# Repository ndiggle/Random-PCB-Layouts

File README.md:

# Random-PCB-Layouts

## Objective
I've uploaded some PCB layouts that I've done in Eagle and KiCad over the past few months. The majority of these layouts were done for pedagogical purposes, but feel free to use any of the designs for alternate uses.

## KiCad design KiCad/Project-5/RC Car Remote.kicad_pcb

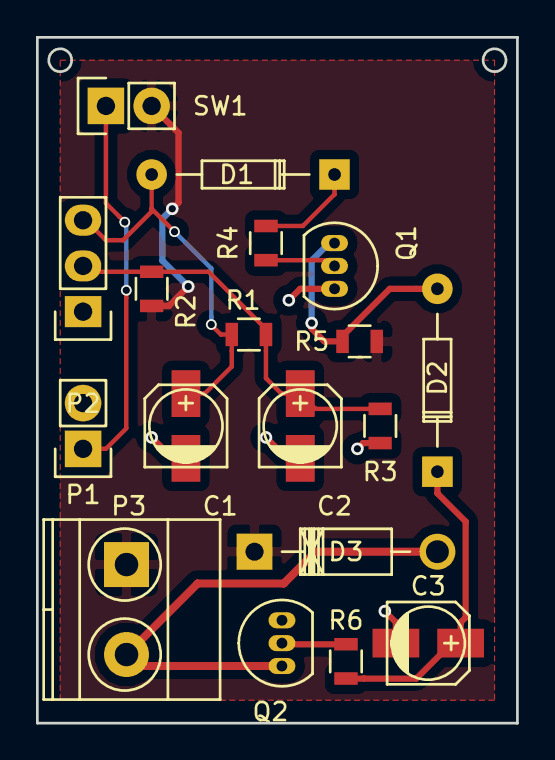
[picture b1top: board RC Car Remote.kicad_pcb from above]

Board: 2 copper layers, 26.7 x 38.1 mm, 18 parts (0 on the bottom side), 11 nets.

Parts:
C1: 47uF; c_elec_4x5.7
C2: 22uF; c_elec_4x5.7
C3: 4.7uF; c_elec_4x5.7
D1, D2: 1N4148; Diode_DO-35_SOD27_Horizontal_RM10
D3: 1N4007; Diode_DO-41_SOD81_Horizontal_RM10
P1: BATT; Pin_Header_Straight_1x02
P2: IR_Reciever; Pin_Header_Straight_1x03
P3: NC_Motor_Relay; TerminalBlock_Pheonix_MKDS1.5-2pol
Q1, Q2: BC548; TO-92_Inline_Narrow_Oval
R1: 33k; R_0805
R2: 560; R_0805
R3: 100k; R_0805
R4: 47k; R_0805
R5, R6: 10k; R_0805
SW1: SPST; Socket_Strip_Straight_1x02

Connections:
+6V: D3.1, P3.1, R2.1, R5.2, SW1.2
/Rly1: D3.2, P3.2, Q2.1
GND: C1.2, C2.2, C3.2, P1.2, P2.1, Q1.3, Q2.3, R3.2
IR_R_2: C2.1, P2.2, R1.1, R2.2, R3.1
IR_R_3: C1.1, D1.2, P2.3, R1.2
unnamed: C3.1, D2.1, R6.2
unnamed: D1.1, R4.2
unnamed: D2.2, Q1.1, R5.1
unnamed: P1.1, SW1.1
unnamed: Q1.2, R4.1
unnamed: Q2.2, R6.1

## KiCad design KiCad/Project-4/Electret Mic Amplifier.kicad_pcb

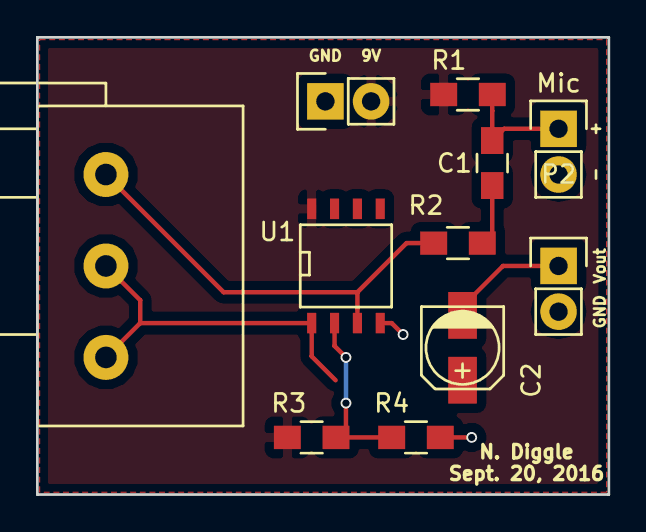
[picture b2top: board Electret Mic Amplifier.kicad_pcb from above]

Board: 2 copper layers, 31.8 x 25.4 mm, 11 parts (0 on the bottom side), 8 nets.

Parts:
C1: 0.1uF; C_0805_HandSoldering
C2: 4.7uF; c_elec_4x5.3
Mic: EM-6022P; Pin_Header_Straight_1x02
P1, P2: CONN_01X02; Pin_Header_Straight_1x02
R1, R3, R4: 10k; R_0805_HandSoldering
R2: 1k; R_0805_HandSoldering
RV1: 100k; Potentiometer_Alps-RK163-single_15mm
U1: LM358; SOIC-8-N

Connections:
+9V: P1.2, R1.1, R3.2, U1.8
/V+: R2.1, RV1.1, U1.3
/V-: R3.1, R4.2, U1.2
/Vfb: C2.1, RV1.2, RV1.3, U1.1
/Vin: C1.2, Mic.1, R1.2
/Vout: C2.2, P2.1
GND: Mic.2, P1.1, P2.2, R4.1, U1.4
unnamed: C1.1, R2.2

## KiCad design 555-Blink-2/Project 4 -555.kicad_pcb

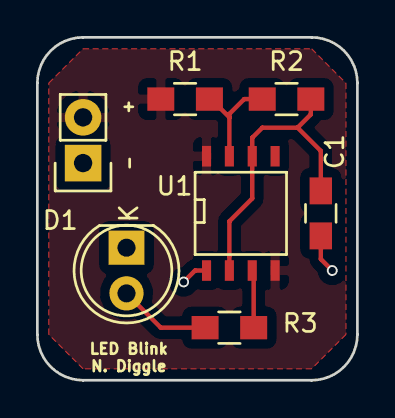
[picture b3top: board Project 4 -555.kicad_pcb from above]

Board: 2 copper layers, 17.8 x 19.0 mm, 7 parts (0 on the bottom side), 6 nets.

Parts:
C1: 1uF; C_0805_HandSoldering
D1: LED; LED-5MM
P1: CONN_01X02; Socket_Strip_Straight_1x02
R1, R3: 1k; R_0805_HandSoldering
R2: 470k; R_0805_HandSoldering
U1: ICM7555; SOIC-8-N

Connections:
GND: C1.2, D1.1, P1.1, U1.1
unnamed: C1.1, R2.2, U1.2, U1.6
unnamed: D1.2, R3.2
unnamed: R1.2, R2.1, U1.7
unnamed: R3.1, U1.3
VCC: P1.2, R1.1, U1.4, U1.8

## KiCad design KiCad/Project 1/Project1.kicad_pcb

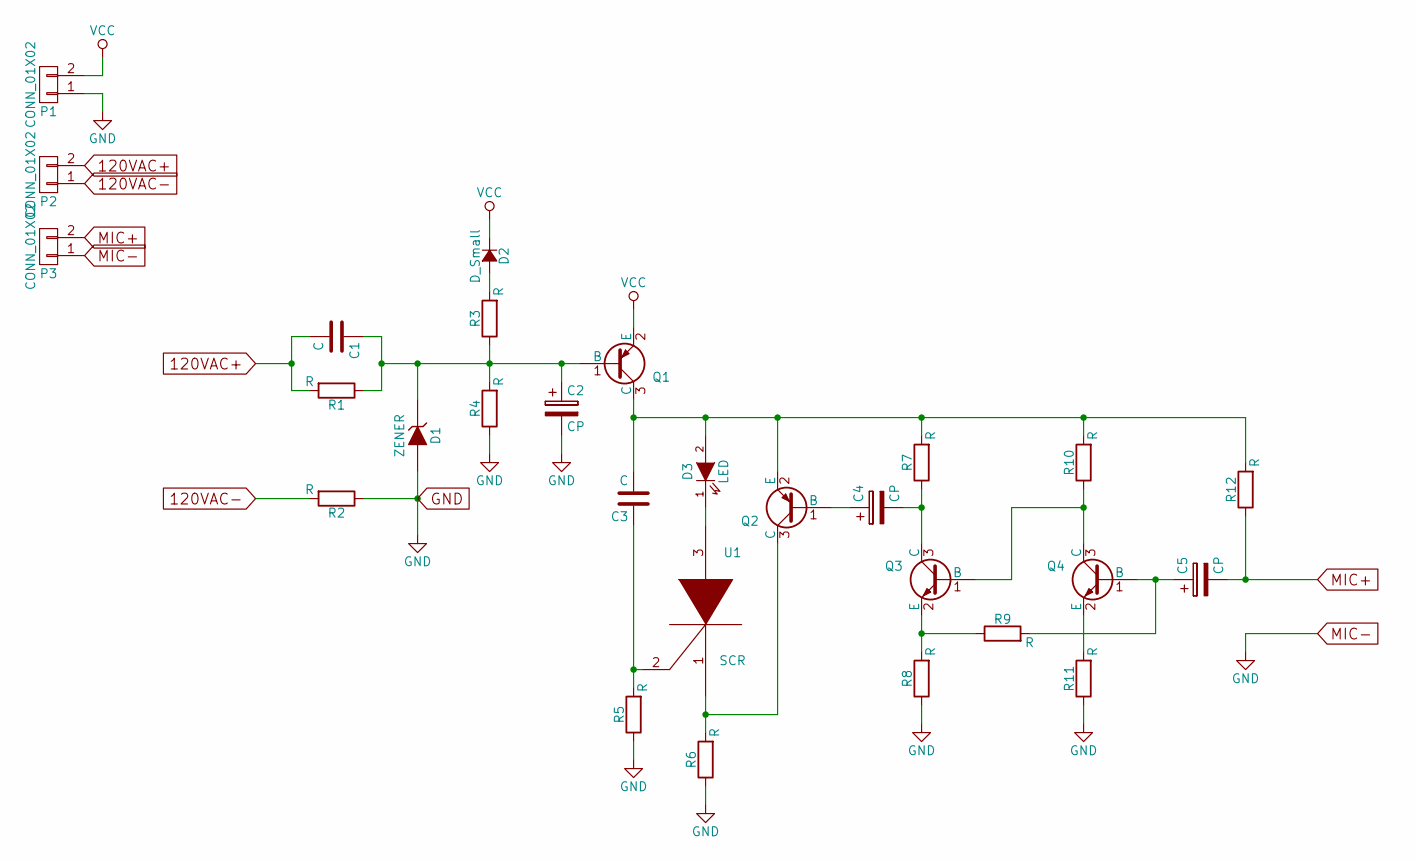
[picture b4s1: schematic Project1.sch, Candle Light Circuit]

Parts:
C1: C; c_elec_8x10
C2, C4, C5: CP; c_elec_8x10
C3: C; C_0805
D1: ZENER; SMB_Handsoldering
D2: D_Small; Diode_DO-41_SOD81_Vertical_AnodeUp
D3: LED; LED-5MM
P1, P2, P3: CONN_01X02; Pin_Header_Straight_1x02
Q1, Q2: MMBT3906; SOT-23_Handsoldering
Q3, Q4: MMBT3904; SOT-23_Handsoldering
R1, R2, R3, R4, R5, R6, R7, R8, R9, R10, R11, R12: R; R_0805_HandSoldering
U1: SCR; TO-220_Neutral123_Vertical

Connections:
120VAC+: C1.2, P2.2, R1.2
120VAC-: P2.1, R2.2
GND: C2.2, D1.2 (A), P1.1, P3.1, R2.1, R4.1, R5.1, R6.1, R8.1, R11.1
MIC+: C5.2, P3.2, R12.1
unnamed: C1.1, C2.1, D1.1 (K), Q1.1 (B), R1.1, R3.1, R4.2
unnamed: C3.1, R5.2, U1.2 (G)
unnamed: C3.2, D3.2 (A), Q1.3 (C), Q2.2 (E), R7.2, R10.2, R12.2
unnamed: C4.1, Q2.1 (B)
unnamed: C4.2, Q3.3 (C), R7.1
unnamed: C5.1, Q4.1 (B), R9.2
unnamed: D2.2 (A), R3.2
unnamed: D3.1 (K), U1.3 (A)
unnamed: Q2.3 (C), R6.2, U1.1 (K)
unnamed: Q3.1 (B), Q4.3 (C), R10.1
unnamed: Q3.2 (E), R8.2, R9.1
unnamed: Q4.2 (E), R11.2
VCC: D2.1 (K), P1.2, Q1.2 (E)

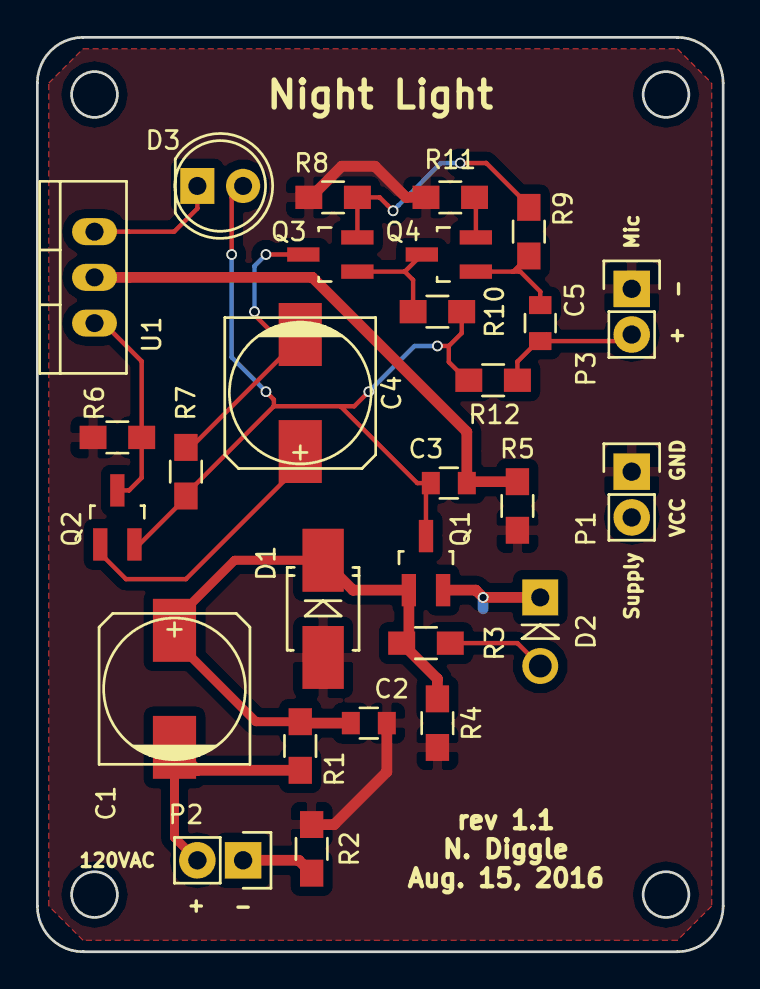
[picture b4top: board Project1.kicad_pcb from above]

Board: 2 copper layers, 38.1 x 50.8 mm, 28 parts (0 on the bottom side), 17 nets.

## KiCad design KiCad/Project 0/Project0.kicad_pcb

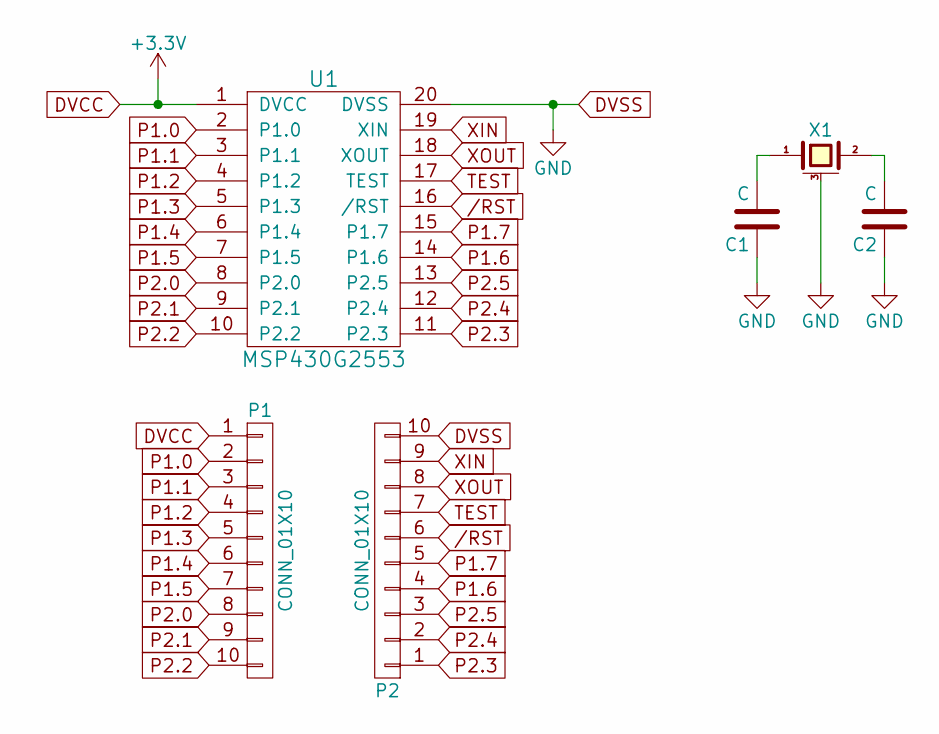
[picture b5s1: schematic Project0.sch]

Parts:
C1, C2: C; C_0805_HandSoldering
P1, P2: CONN_01X10; Pin_Header_Straight_1x10
U1: MSP430G2553; SSOP-20
X1: CRYSTAL_SMD; Crystal_HC49-U_Vertical_3Pin

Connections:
/RST: P2.6, U1.16 (/RST)
DVCC: P1.1, U1.1 (DVCC)
DVSS: C1.1, C2.1, P2.10, U1.20 (DVSS), X1.3 (case)
unnamed: C1.2, X1.1
unnamed: C2.2, X1.2
P1.0: P1.2, U1.2 (P1.0)
P1.1: P1.3, U1.3 (P1.1)
P1.2: P1.4, U1.4 (P1.2)
P1.3: P1.5, U1.5 (P1.3)
P1.4: P1.6, U1.6 (P1.4)
P1.5: P1.7, U1.7 (P1.5)
P1.6: P2.4, U1.14 (P1.6)
P1.7: P2.5, U1.15 (P1.7)
P2.0: P1.8, U1.8 (P2.0)
P2.1: P1.9, U1.9 (P2.1)
P2.2: P1.10, U1.10 (P2.2)
P2.3: P2.1, U1.11 (P2.3)
P2.4: P2.2, U1.12 (P2.4)
P2.5: P2.3, U1.13 (P2.5)
TEST: P2.7, U1.17 (TEST)
XIN: P2.9, U1.19 (XIN)
XOUT: P2.8, U1.18 (XOUT)

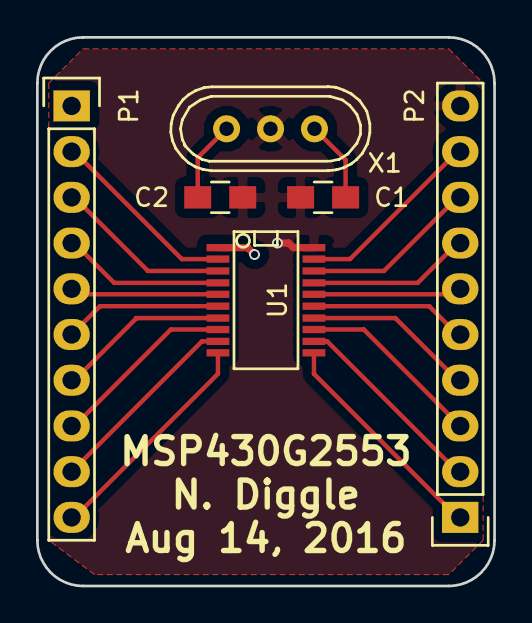
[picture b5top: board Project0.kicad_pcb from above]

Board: 2 copper layers, 25.4 x 30.5 mm, 6 parts (0 on the bottom side), 22 nets.

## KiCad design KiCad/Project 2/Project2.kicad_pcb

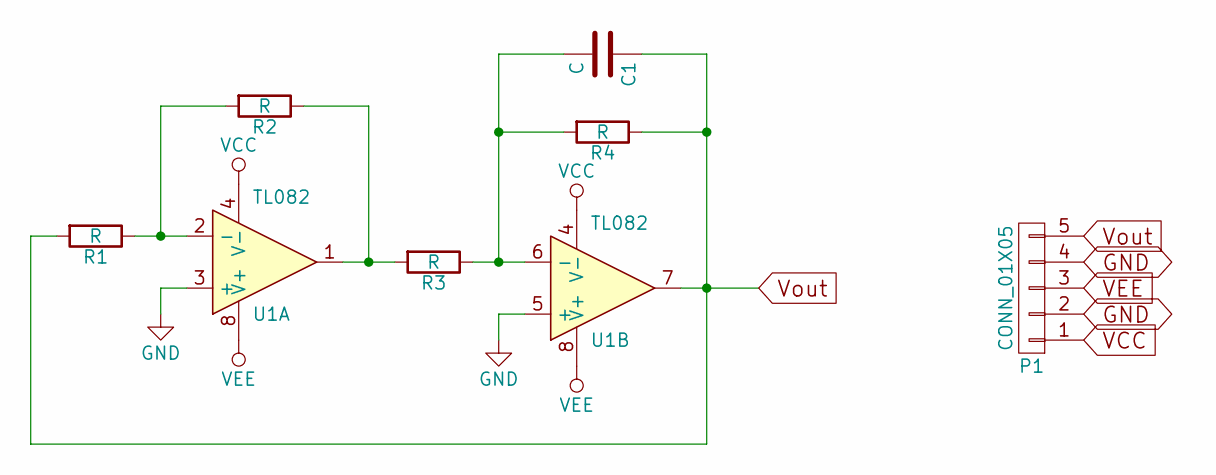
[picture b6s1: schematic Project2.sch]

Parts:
C1: C; C_0805_HandSoldering
P1: CONN_01X05; Pin_Header_Straight_1x05
R1, R2, R3, R4: R; R_0805_HandSoldering
U1: TL082; SOIC-8-N

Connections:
GND: P1.2, P1.4, U1.3 (+), U1.5 (+)
unnamed: C1.2, R3.1, R4.2, U1.6 (-)
unnamed: R1.1, R2.2, U1.2 (-)
unnamed: R2.1, R3.2, U1.1
VCC: P1.1, U1.4 (V-)
VEE: P1.3, U1.8 (V+)
Vout: C1.1, P1.5, R1.2, R4.1, U1.7

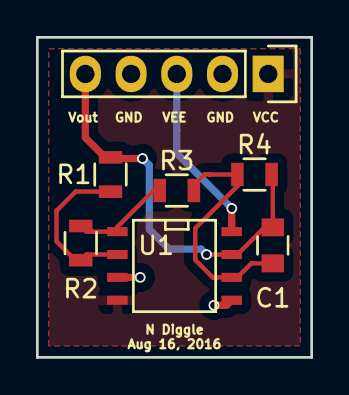
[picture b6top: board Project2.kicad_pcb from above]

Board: 2 copper layers, 15.2 x 17.8 mm, 7 parts (0 on the bottom side), 7 nets.

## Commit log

2016-07-29 Rename bbSch1.brd to Buck-Boost-Prototype/bbSch1.brd
2016-07-29 Rename bbSch1.sch to Buck-Boost-Prototype/bbSch1.sch
2016-07-29 Rename headphone_amp.brd to Mini-Headphone-Amplifier/headphone_amp.brd
2016-07-29 Rename headphone_amp.sch to Mini-Headphone-Amplifier/headphone_amp.sch
2016-07-29 Rename vlpf.brd to Audio-LPF/vlpf.brd
2016-07-29 Rename vlpf.sch to Audio-LPF/vlpf.sch
2016-07-29 Rename 555_led_pcb.brd to 555-Blink-Test/555_led_pcb.brd
2016-07-29 Rename 555_led_schematic.sch to 555-Blink-Test/555_led_schematic.sch
2016-07-29 Create tempFile
2016-07-29 Create tempfile
2016-07-31 Added new schematic/PCB for Audio Comrpessor
2016-08-02 Added new sch/pcb
2016-08-19 Added new KiCad layouts
2016-08-19 Sorting out issue with commits
2016-08-19 Deleted the temporary file
2016-08-19 Put all Eagle files into their own directory
2016-08-30 Added datasheet to be used for refference.
2016-09-09 Create Temp
2016-09-26 Added RC car remote sch/pcb
2016-09-26 Reorganized folders and renamed 555 kicad project
2016-09-26 Separated Eagle and Kicad files into seprate folders.
